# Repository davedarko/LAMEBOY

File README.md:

# LAMEBOY
https://hackaday.io/project/26823-lameboy-another-esp12-handheld

Ever since https://hackaday.io/project/18648-nokia-3310-5110-display-board I've wanted to slap on an ESP module and some buttons to make a nice little portable handheld. Now with some googling and checking out other projects how they get their stuff done and a bit time on hand while on vacation I'm using every spare minute to work on this PCB. There are some minor things I'm not sure about that need testing, but the general concept is clear.

The last version - R 3.2.3 - seems to got lost, it was rebranded to Game Toy and some pinouts were changed to make more sense.

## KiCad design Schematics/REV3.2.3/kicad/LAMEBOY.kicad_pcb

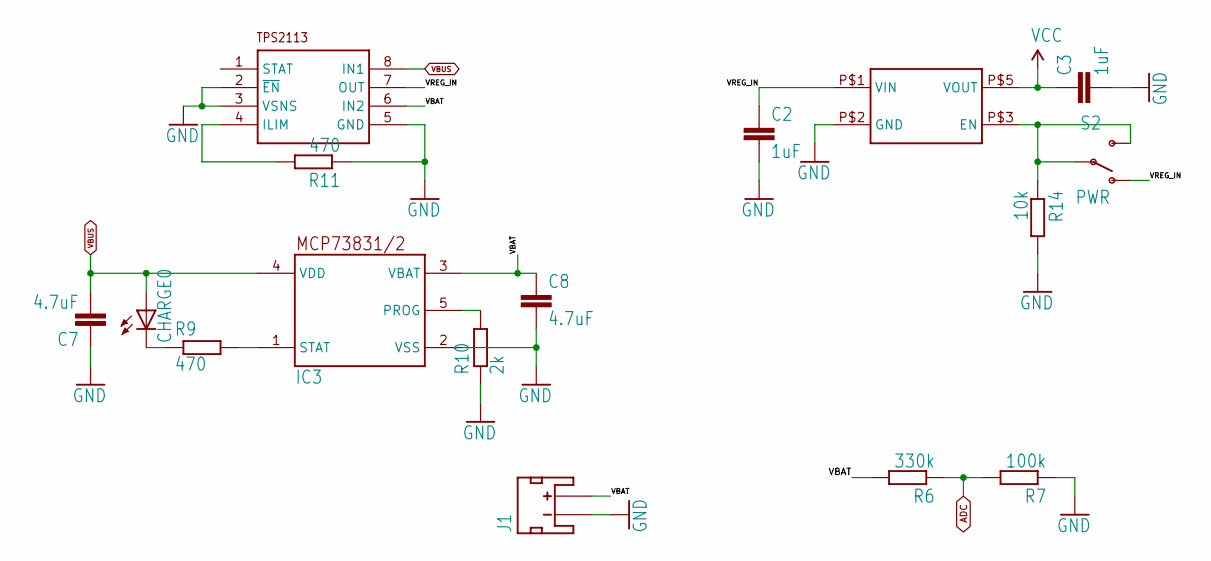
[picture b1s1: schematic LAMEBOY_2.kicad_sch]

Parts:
C2, C3: 1uF; C0805
C7, C8: 4.7uF; C0805
CHARGE0: LEDCHARLIE; CHIPLED_0603_CHARLIE
IC3: MCP73831; SOT23-5L
J1: JST_2MM_MALE; JST-2-SMD
R6: 330k; R0603
R7: 100k; R0603
R9, R11: 470; R0603
R10: 2k; R0603
R14: 10k; R0603
S2: PWR; SWITCH-SPST-SMD-A
U$4: TPS2113-PW; TEXAS-PW
U$9: AP2112KAP2112K; AP2112

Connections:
ADC: R6.1, R7.2; also elsewhere on the board
GND: C2.2, C3.2, C7.1, C8.2, IC3.2 (VSS), J1.1 (-), R7.1, R10.1, R11.1, R14.2, U$4.2 (~EN), U$4.3 (VSNS), U$4.5 (GND), U$9.P$2 (GND); also elsewhere on the board
unnamed: IC3.1 (STAT), R9.2
unnamed: CHARGE0.C, R9.1
unnamed: R11.2, U$4.4 (ILIM)
unnamed: IC3.5 (PROG), R10.2
VBAT: C8.1, IC3.3 (VBAT), J1.2 (+), R6.2, U$4.6 (IN2)
VBUS: C7.2, CHARGE0.A, IC3.4 (VDD), U$4.8 (IN1); also elsewhere on the board
VCC: C3.1, U$9.P$5 (VOUT); also elsewhere on the board
VREG_EN: R14.1, S2.2, S2.3 (S), U$9.P$3 (EN)
VREG_IN: C2.1, S2.1 (O), U$4.7 (OUT), U$9.P$1 (VIN)

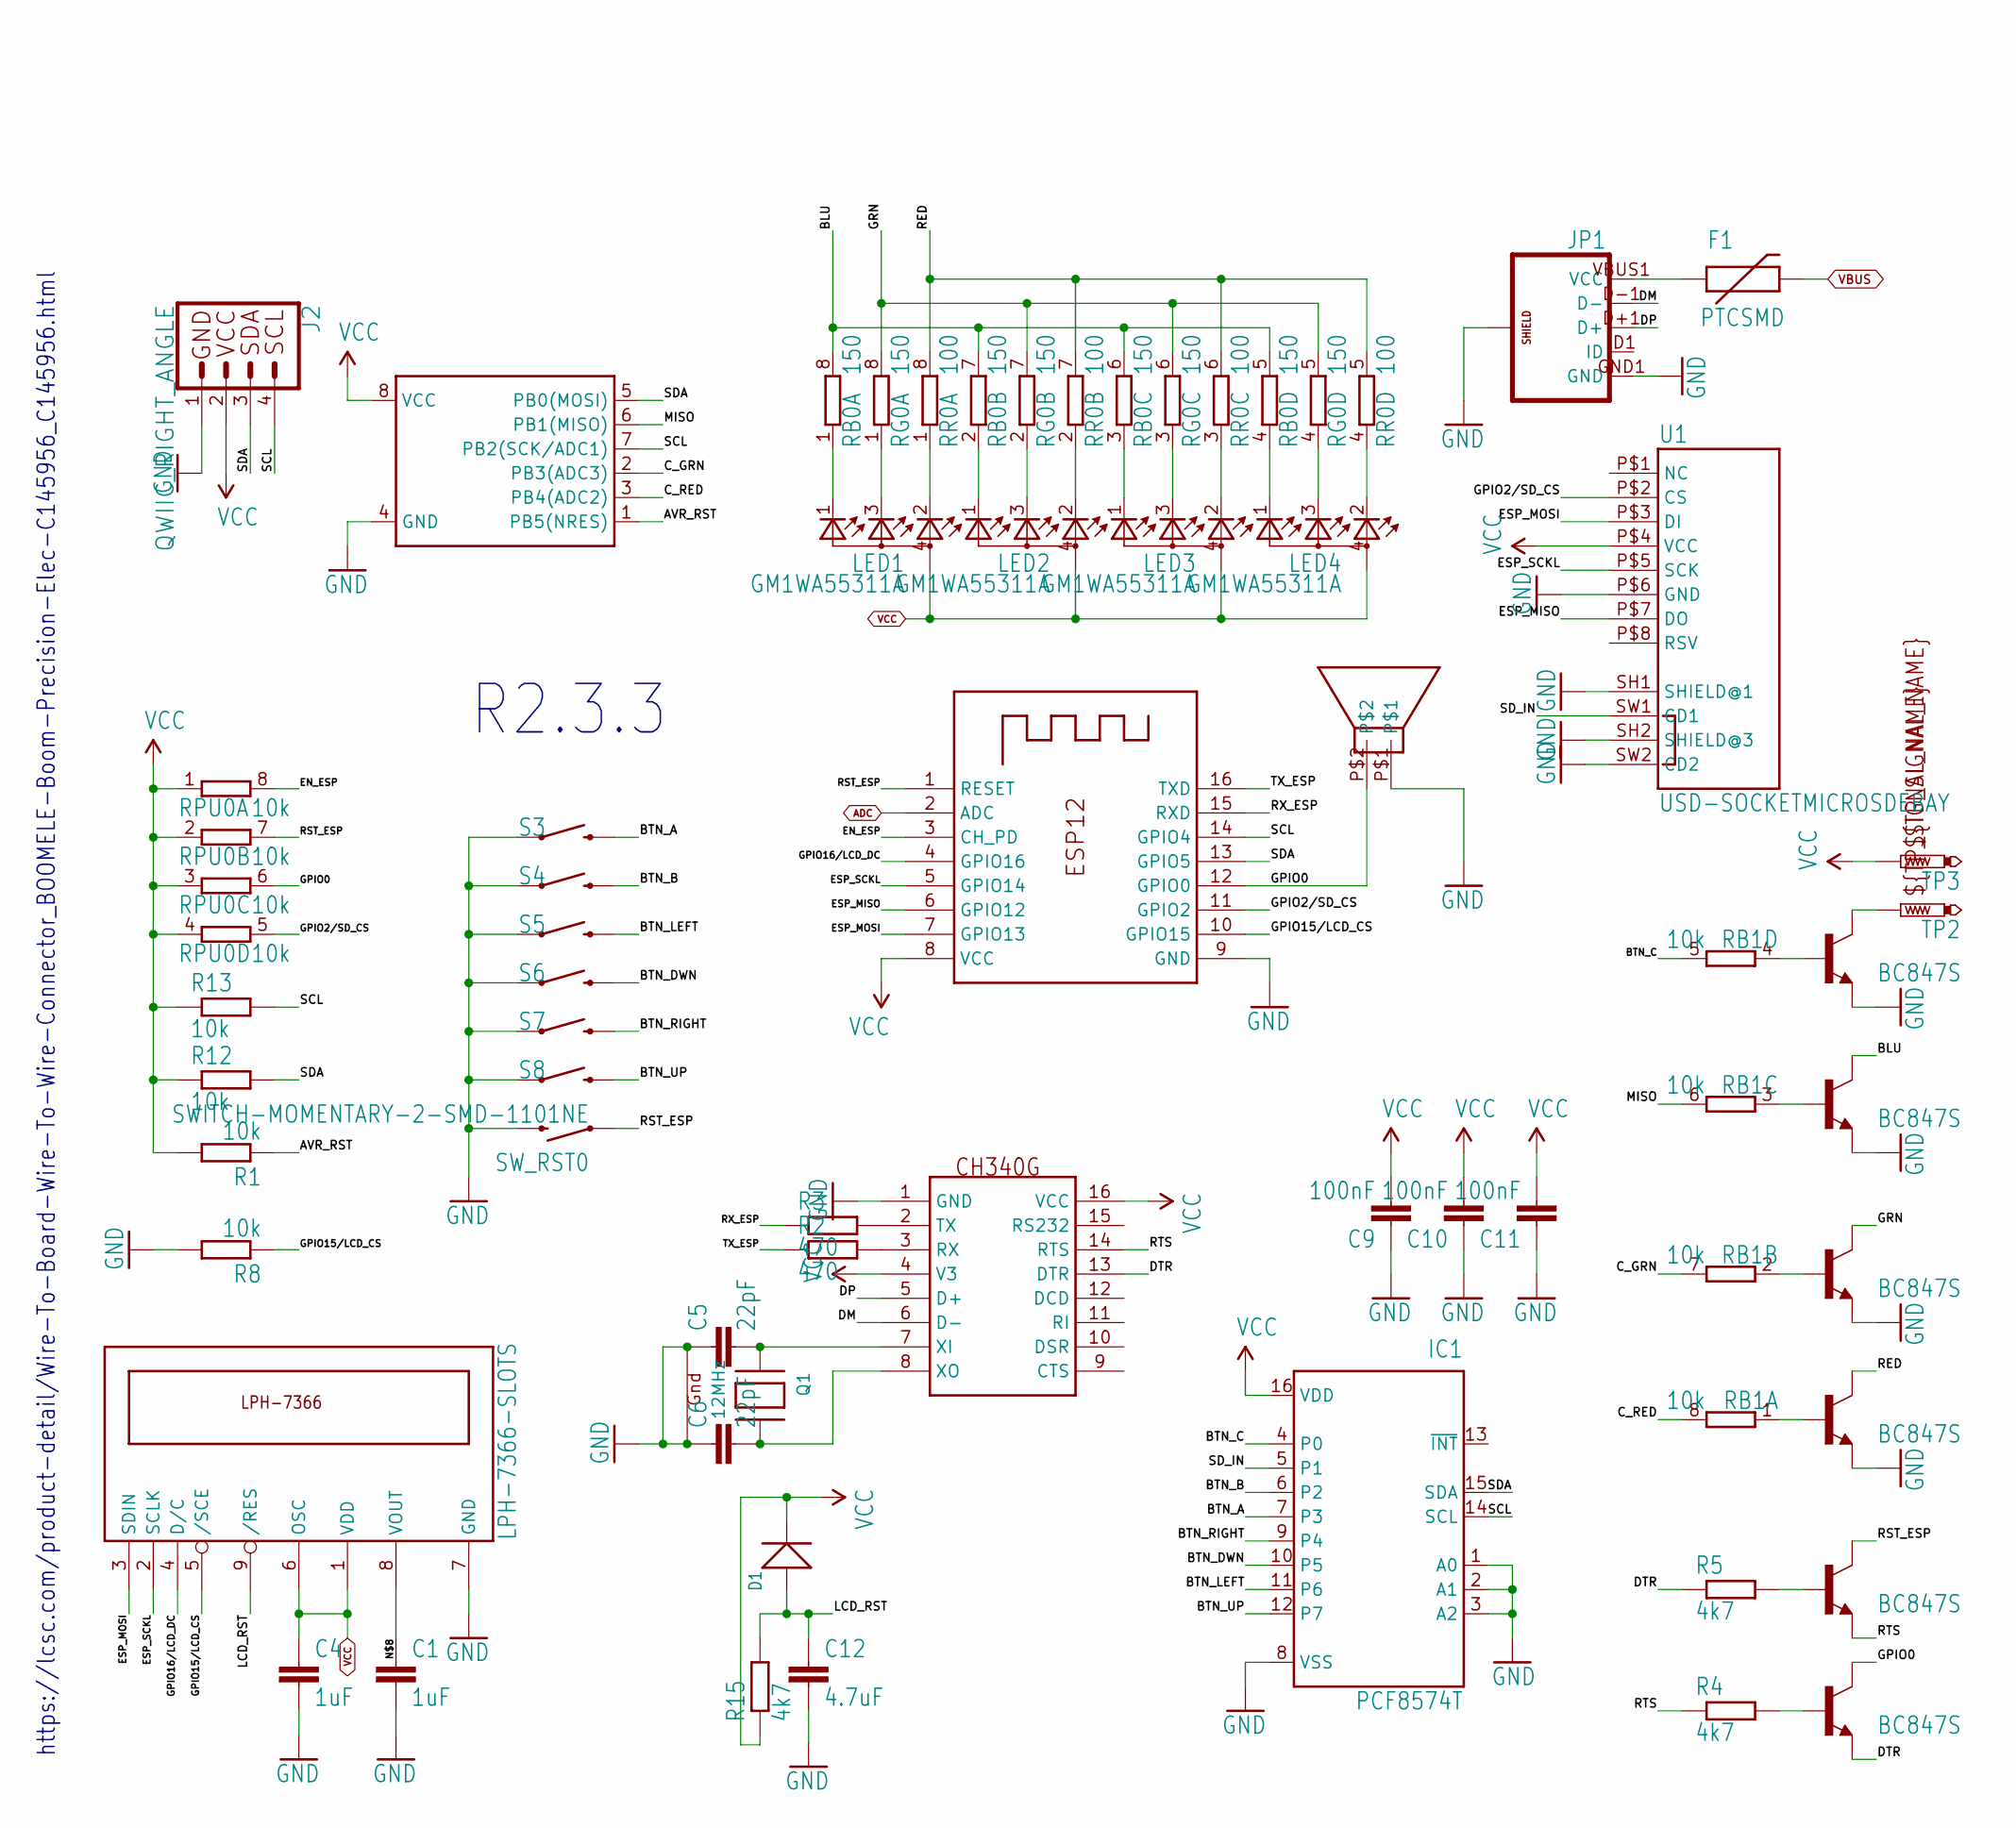
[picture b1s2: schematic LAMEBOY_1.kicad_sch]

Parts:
C1, C4: 1uF; C0805
C5, C6: 22pF; C0805
C9, C10, C11: 100nF; C0805
C12: 4.7uF; C0805
CH340G0: CH340GCH340G; SOIC16
D1: DIODE'1N4148-SMD'; LL-34
F1: PTCSMD; PTC-1206
IC1: PCF8574T; SO16W
J2: QWIIC_RIGHT_ANGLE; JST04_1MM_RA
JP1: USB_MICROB_PLUG-IDK; USB-AB-MICRO-SMD_SLOT
LED1, LED2, LED3, LED4: GM1WA55311A
Q1: 12MHz; NX3225_BIGGER
R1, R8, R12, R13: 10k; R0603
R2, R3: 470; R0603
R4, R5, R15: 4k7; R0603
RB0: 150; 0603-ARC
RB1: 10k; 0603-ARC
RG0: 150; 0603-ARC
RPU0: 10k; 0603-ARC
RR0: 100; 0603-ARC
S3, S4, S5, S6, S7, S8: SWITCH-MOMENTARY-2SMD-4; TACTILE_SWITCH_TALL
SW_RST0: SWITCH-MOMENTARY-2-SMD-1101NE; TACTILE-SWITCH-1101NE
TP2, TP3: PTR1B1,27; B1,27
U1: USD-SOCKETMICROSDEBAY; MICRO-SD-SOCKET-EBAY
U$1: LPH-7366-SLOTS
U$2: ATTINY13SO08-WIDE; SO08-EIAJ
U$3, U$6, U$7: BC847S; SOT363
U$5: SPEAKERKMTG-1102; KMTG-1102
X1: ESP-12

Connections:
ADC: X1.2 (ADC); also elsewhere on the board
AVR_RST: R1.1, U$2.1 (PB5(NRES))
BLU: RB0.5 (2), RB0.6 (2), RB0.7 (2), RB0.8 (2), U$7.3 (C)
BLUE_LED: LED4.1 (CGREEN), RB0.4 (1)
BTN_A: IC1.7 (P3), S3.B2 (2)
BTN_B: IC1.6 (P2), S4.B2 (2)
BTN_C: IC1.4 (P0), RB1.5 (2)
BTN_DWN: IC1.10 (P5), S6.B2 (2)
BTN_LEFT: IC1.11 (P6), S5.B2 (2)
BTN_RIGHT: IC1.9 (P4), S7.B2 (2)
BTN_UP: IC1.12 (P7), S8.B2 (2)
C_GRN: RB1.7 (2), U$2.2 (PB3(ADC3))
C_RED: RB1.8 (2), U$2.3 (PB4(ADC2))
DM: CH340G0.6 (D-), JP1.D-1 (D-)
DP: CH340G0.5 (D+), JP1.D+1 (D+)
DTR: CH340G0.13 (DTR), R5.1, U$3.1 (E)
EN_ESP: RPU0.8 (2), X1.3 (CH_PD)
ESP_MISO: U1.P$7 (DO), X1.6 (GPIO12)
ESP_MOSI: U1.P$3 (DI), U$1.3 (SDIN), X1.7 (GPIO13)
ESP_SCKL: U1.P$5 (SCK), U$1.2 (SCLK), X1.5 (GPIO14)
GND: C1.2, C4.2, C5.1, C6.1, C9.1, C10.1, C11.1, C12.2, CH340G0.1 (GND), IC1.1 (A0), IC1.2 (A1), IC1.3 (A2), IC1.8 (VSS), J2.1, JP1.GND1 (GND), JP1.P$1 (SHIELD), JP1.P$2 (SHIELD), JP1.P$3 (SHIELD), JP1.P$4 (SHIELD), Q1.2 (G2), Q1.4 (G1), R8.2, S3.A2 (1), S4.A2 (1), S5.A2 (1), S6.A2 (1), S7.A2 (1), S8.A2 (1), SW_RST0.P$2 (2), U1.P$6 (GND), U1.SH1 (SHIELD@1), U1.SH2 (SHIELD@3), U1.SW2 (CD2), U$1.7 (GND), U$2.4 (GND), U$5.P$1, U$6.1 (E), U$6.4 (E), U$7.1 (E), U$7.4 (E), X1.9 (GND); also elsewhere on the board
GPIO0: RPU0.6 (2), U$3.6 (C), U$5.P$2, X1.12 (GPIO0)
GPIO2/SD_CS: RPU0.5 (2), U1.P$2 (CS), X1.11 (GPIO2)
GPIO15/LCD_CS: R8.1, U$1.5 (/SCE), X1.10 (GPIO15)
GPIO16/LCD_DC: U$1.4 (D/C), X1.4 (GPIO16)
GREEN_LED: LED4.3 (CBLUE), RG0.4 (1)
GRN: RG0.5 (2), RG0.6 (2), RG0.7 (2), RG0.8 (2), U$6.6 (C)
L2_R: LED1.3 (CBLUE), RG0.1
L3_B: LED1.1 (CGREEN), RB0.1
L4_G: LED1.2 (CRED), RR0.1
LCD_RST: C12.1, D1.A (+), R15.2, U$1.9 (/RES)
MISO: RB1.6 (2), U$2.6 (PB1(MISO))
unnamed: LED3.1 (CGREEN), RB0.3 (1)
unnamed: LED3.3 (CBLUE), RG0.3 (1)
unnamed: LED3.2 (CRED), RR0.3 (1)
unnamed: LED2.1 (CGREEN), RB0.2 (1)
unnamed: C1.1, U$1.8 (VOUT)
unnamed: LED2.3 (CBLUE), RG0.2 (1)
unnamed: LED2.2 (CRED), RR0.2 (1)
unnamed: RB1.1, U$6.5 (B)
unnamed: RB1.2 (1), U$6.2 (B)
unnamed: TP2.TP, U$7.6 (C)
unnamed: C5.2, CH340G0.7 (XI), Q1.1 (X1)
unnamed: RB1.3 (1), U$7.5 (B)
unnamed: RB1.4 (1), U$7.2 (B)
unnamed: C6.2, CH340G0.8 (XO), Q1.3 (X2)
unnamed: R5.2, U$3.5 (B)
unnamed: CH340G0.3 (RX), R2.2
unnamed: CH340G0.2 (TX), R3.2
unnamed: R4.2, U$3.2 (B)
RED: RR0.5 (2), RR0.6 (2), RR0.7 (2), RR0.8 (2), U$6.3 (C)
RED_LED: LED4.2 (CRED), RR0.4 (1)
RST_ESP: RPU0.7 (2), SW_RST0.P$1 (1), U$3.3 (C), X1.1 (RESET)
RTS: CH340G0.14 (RTS), R4.1, U$3.4 (E)
RX_ESP: R3.1, X1.15 (RXD)
SCL: IC1.14 (SCL), J2.4, R13.2, U$2.7 (PB2(SCK/ADC1)), X1.14 (GPIO4)
SDA: IC1.15 (SDA), J2.3, R12.2, U$2.5 (PB0(MOSI)), X1.13 (GPIO5)
SD_IN: IC1.5 (P1), U1.SW1 (CD1)
TX_ESP: R2.1, X1.16 (TXD)
VBUS: F1.2; also elsewhere on the board
VCC: C4.1, C9.2, C10.2, C11.2, CH340G0.4 (V3), CH340G0.16 (VCC), D1.C (-), IC1.16 (VDD), J2.2, LED1.4 (A), LED2.4 (A), LED3.4 (A), LED4.4 (A), R1.2, R12.1, R13.1, R15.1, RPU0.1, RPU0.2 (1), RPU0.3 (1), RPU0.4 (1), TP3.TP, U1.P$4 (VCC), U$1.1 (VDD), U$1.6 (OSC), U$2.8 (VCC), X1.8 (VCC); also elsewhere on the board
VUSB: F1.1, JP1.VBUS1 (VCC)

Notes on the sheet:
R2.3.3
https://lcsc.com/product-detail/Wire-To-Board-Wire-To-Wire-Connector_BOOMELE-Boom-Precision-Elec-C145956_C145956.html

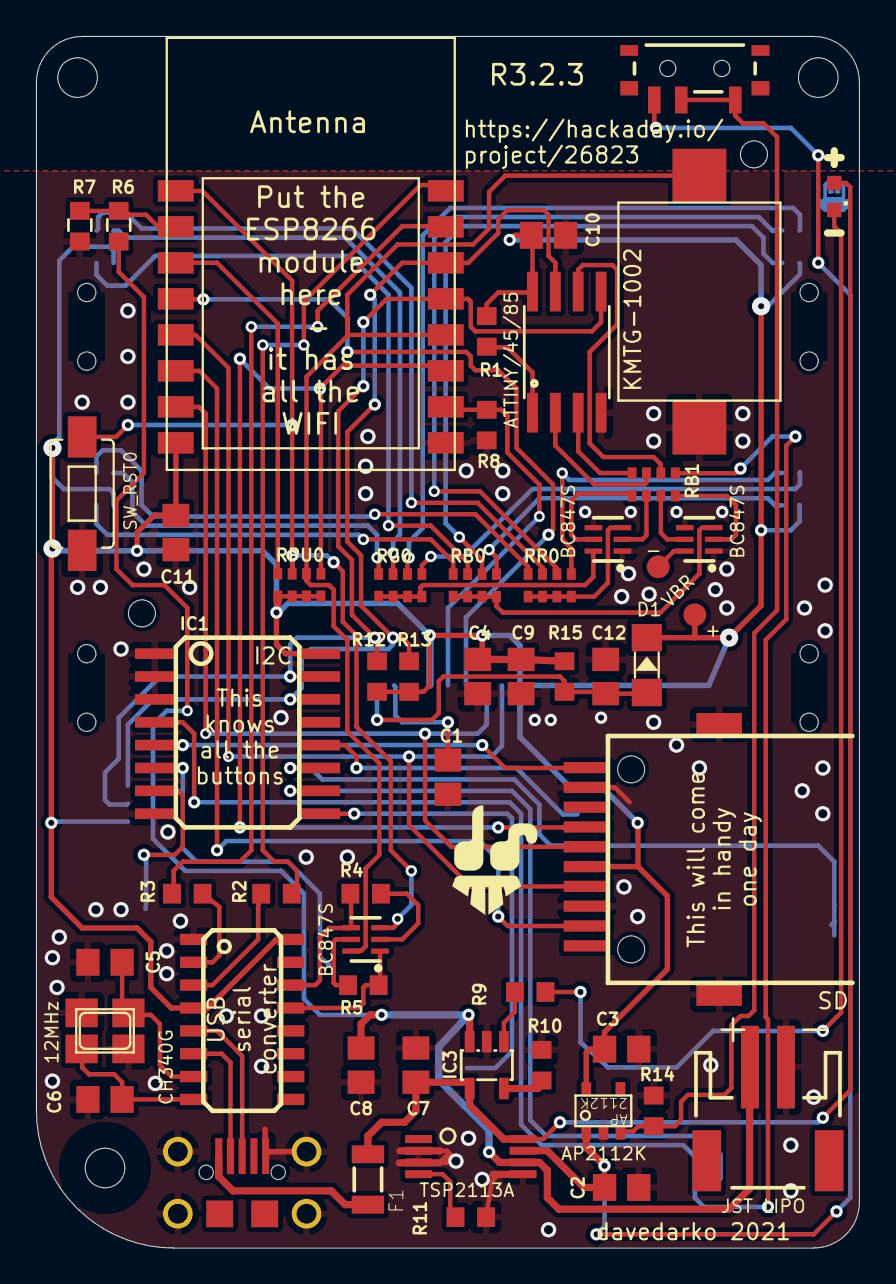
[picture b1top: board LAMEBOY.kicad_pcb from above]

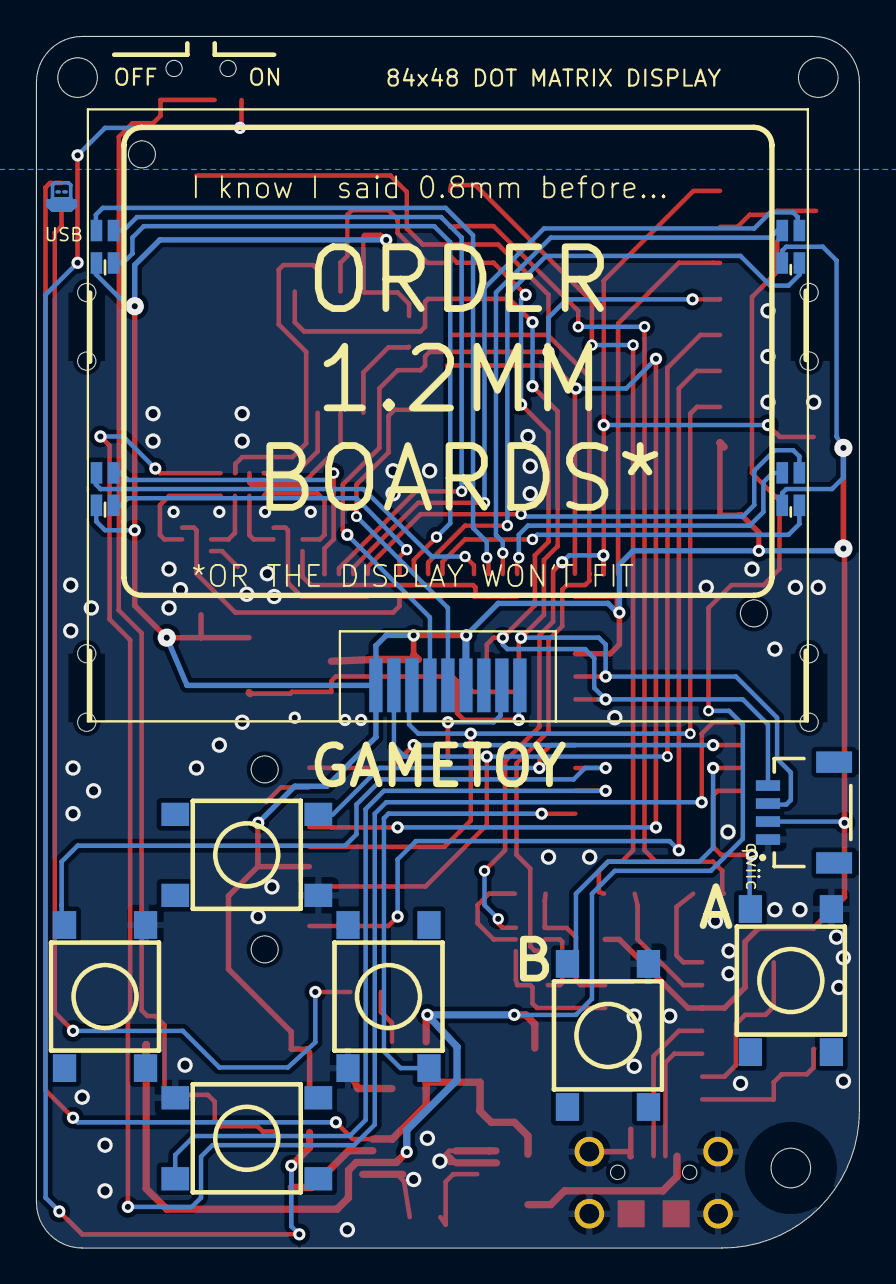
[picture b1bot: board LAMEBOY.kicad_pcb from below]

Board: 2 copper layers, 45.7 x 67.3 mm, 71 parts (13 on the bottom side), 69 nets.

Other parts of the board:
@HOLE0, @HOLE1, @HOLE2: (no value)
U$11: DAVEDARKO2_LOGO
U$13: DAVEDARKO_GOLD

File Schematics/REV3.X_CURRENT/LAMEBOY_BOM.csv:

"Qty";"Value";"Device";"Package";"Parts";"Description";"MF";"MPN";"OC_FARNELL";"OC_NEWARK";"PROD_ID";
"1";"";"ESP-12";"ESP-12";"X1";"";"";"";"";"";"";
"1";"";"JST_2MM_MALE";"JST-2-SMD";"J1";"Mates to single-cell LiPo batteries.";"";"";"";"";"CONN-08352";
"1";"";"LEDCHARLIE";"CHIPLED_0603_CHARLIE";"CHARGE";"LED";"";"";"";"";"";
"2";"";"SWITCH-MOMENTARY-2-SMD-1101NE";"TACTILE-SWITCH-1101NE";"SW_C, SW_RST";"Various NO switches- pushbuttons, reed, etc";"";"";"";"";"";
"1";"100";"4R-N0603-ARC";"0603-ARC";"RR";"Array Chip Resistor";"";"";"unknown";"unknown";"";
"1";"100k";"R-EU_ONEFITSALL";"ONEFITSALL";"R7";"RESISTOR, European symbol";"";"";"";"";"";
"3";"100nF";"C-EUONEFITSALL";"ONEFITSALL";"C9, C10, C11";"CAPACITOR, European symbol";"";"";"";"";"";
"2";"10k";"4R-N0603-ARC";"0603-ARC";"RB1, RPU";"Array Chip Resistor";"";"";"unknown";"unknown";"";
"5";"10k";"R-EU_ONEFITSALL";"ONEFITSALL";"R1, R8, R12, R13, R14";"RESISTOR, European symbol";"";"";"";"";"";
"1";"12MHz";"XTAL-4BIGGER";"NX3225_BIGGER";"Q1";"Classic 4-pin 3.2 x 2.5mm crystal";"";"";"";"";"";
"2";"150";"4R-N0603-ARC";"0603-ARC";"RB, RG";"Array Chip Resistor";"";"";"unknown";"unknown";"";
"4";"1uF";"C-EUONEFITSALL";"ONEFITSALL";"C1, C2, C3, C4";"CAPACITOR, European symbol";"";"";"";"";"";
"2";"22pF";"C-EUONEFITSALL";"ONEFITSALL";"C5, C6";"CAPACITOR, European symbol";"";"";"";"";"";
"1";"2k";"R-EU_ONEFITSALL";"ONEFITSALL";"R10";"RESISTOR, European symbol";"";"";"";"";"";
"1";"330k";"R-EU_ONEFITSALL";"ONEFITSALL";"R6";"RESISTOR, European symbol";"";"";"";"";"";
"2";"4.7uF";"C-EUONEFITSALL";"ONEFITSALL";"C7, C8";"CAPACITOR, European symbol";"";"";"";"";"";
"4";"470";"R-EU_ONEFITSALL";"ONEFITSALL";"R2, R3, R9, R11";"RESISTOR, European symbol";"";"";"";"";"";
"2";"4k7";"R-EU_ONEFITSALL";"ONEFITSALL";"R4, R5";"RESISTOR, European symbol";"";"";"";"";"";
"1";"AP2112KAP2112K";"AP2112KAP2112K";"AP2112";"U$9";"";"";"";"";"";"";
"1";"ATTINY13SO08-WIDE";"ATTINY13SO08-WIDE";"SO08-EIAJ";"U$2";"Atmel 8-pin 1kB flash uC";"";"";"";"";"";
"1";"AVR_SPI_PRG_6";"AVR_SPI_PRG_6";"2X3_SMD_PAD";"JP2";"AVR ISP 6 Pin";"";"";"";"";"";
"3";"BC847S";"MMDT3904";"SOT363";"U$3, U$6, U$7";"Dual NPN transistor";"";"";"";"";"";
"1";"CH340GCH340G";"CH340GCH340G";"SOIC16";"CH340G";"USB to TTL RS232 converter";"";"";"";"";"";
"4";"GM1WA55311A";"GM1WA55311A";"GM1WA55311A";"LED1, LED2, LED3, LED4";"Chip LED RGB";"";"";"";"";"";
"1";"I2C_GROVE";"I2C_GROVE";"I2C_GROVE";"U$10";"";"";"";"";"";"";
"1";"LPH-7366-SLOTS";"LPH-7366-SLOTS";"LPH-7366-SLOTS";"U$1";"";"";"";"";"";"";
"1";"MCP73831";"MCP73831/OT";"SOT23-5L";"IC3";"MCP73831/2";"";"";"";"";"";
"1";"PCF8574T";"PCF8574T";"SO16W";"IC1";"I2C-Bus Remote 8-bit I/O expander";"";"PCF8574T/3,512";"1201255";"70R6870";"";
"1";"PTCSMD";"PTCSMD";"PTC-1206";"F1";"Resettable Fuse PTC";"";"";"";"";"RES-11150";
"1";"PWR";"SWITCH-SPDT-SMD-A";"SWITCH-SPST-SMD-A";"S2";"SPDT Switch";"";"";"";"";"";
"6";"SWITCH-MOMENTARY-2SMD-4";"SWITCH-MOMENTARY-2SMD-4";"TACTILE_SWITCH_TALL";"S3, S4, S5, S6, S7, S8";"Various NO switches- pushbuttons, reed, etc";"";"";"";"";"SWCH-11966";
"1";"TPS2113-PW";"TPS2113-PW";"TEXAS-PW";"U$4";"";"";"";"";"";"";
"1";"USB_MICROB_PLUG-IDK";"USB_MICROB_PLUG-IDK";"USB-AB-MICRO-SMD_SLOT";"JP1";"USB Micro-B connectors";"";"";"";"";"";
"1";"USD-SOCKETMICROSDEBAY";"USD-SOCKETMICROSDEBAY";"MICRO-SD-SOCKET-EBAY";"U1";"microSD Socket";"";"";"";"";"";

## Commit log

2017-09-26 rev2
2017-10-04 bigger better resistor and crystal footprint
2017-10-14 no idea. there's stuff changed so I push.
2017-10-20 idea of an external cartridge
2017-10-20 corrected rgb layout
2017-10-20 moved sd slot slightley
2017-10-20 moved a via :D
2017-10-20 labelstuff
2017-10-21 moved C and RST switch
2017-10-21 usb logo
2017-10-21 read me
2017-10-23 wrong power for enabling regulator
2017-10-25 layerstuff and footprints
2018-01-09 hm, what happened here
2018-01-24 moved 3.1 to 3.X
    added pull down power switch
2018-02-20 minor changes to rev3.1
2018-02-20 rev3.4 sound pins
2018-02-20 external cartridge
2018-02-20 case designs
2018-02-20 attiny binary
2018-02-20 label for batteries
2018-02-20 moar labels
2018-02-21 moaar labels
2018-03-10 current version gerber
2018-03-10 minor footprint changes
2018-03-11 current bom
2019-08-22 sound and vibrator
2019-08-30 bye c
2020-01-10 moved labels
2024-09-05 added KiCad Schematics of R3.2.1
2024-09-08 found the last version!
